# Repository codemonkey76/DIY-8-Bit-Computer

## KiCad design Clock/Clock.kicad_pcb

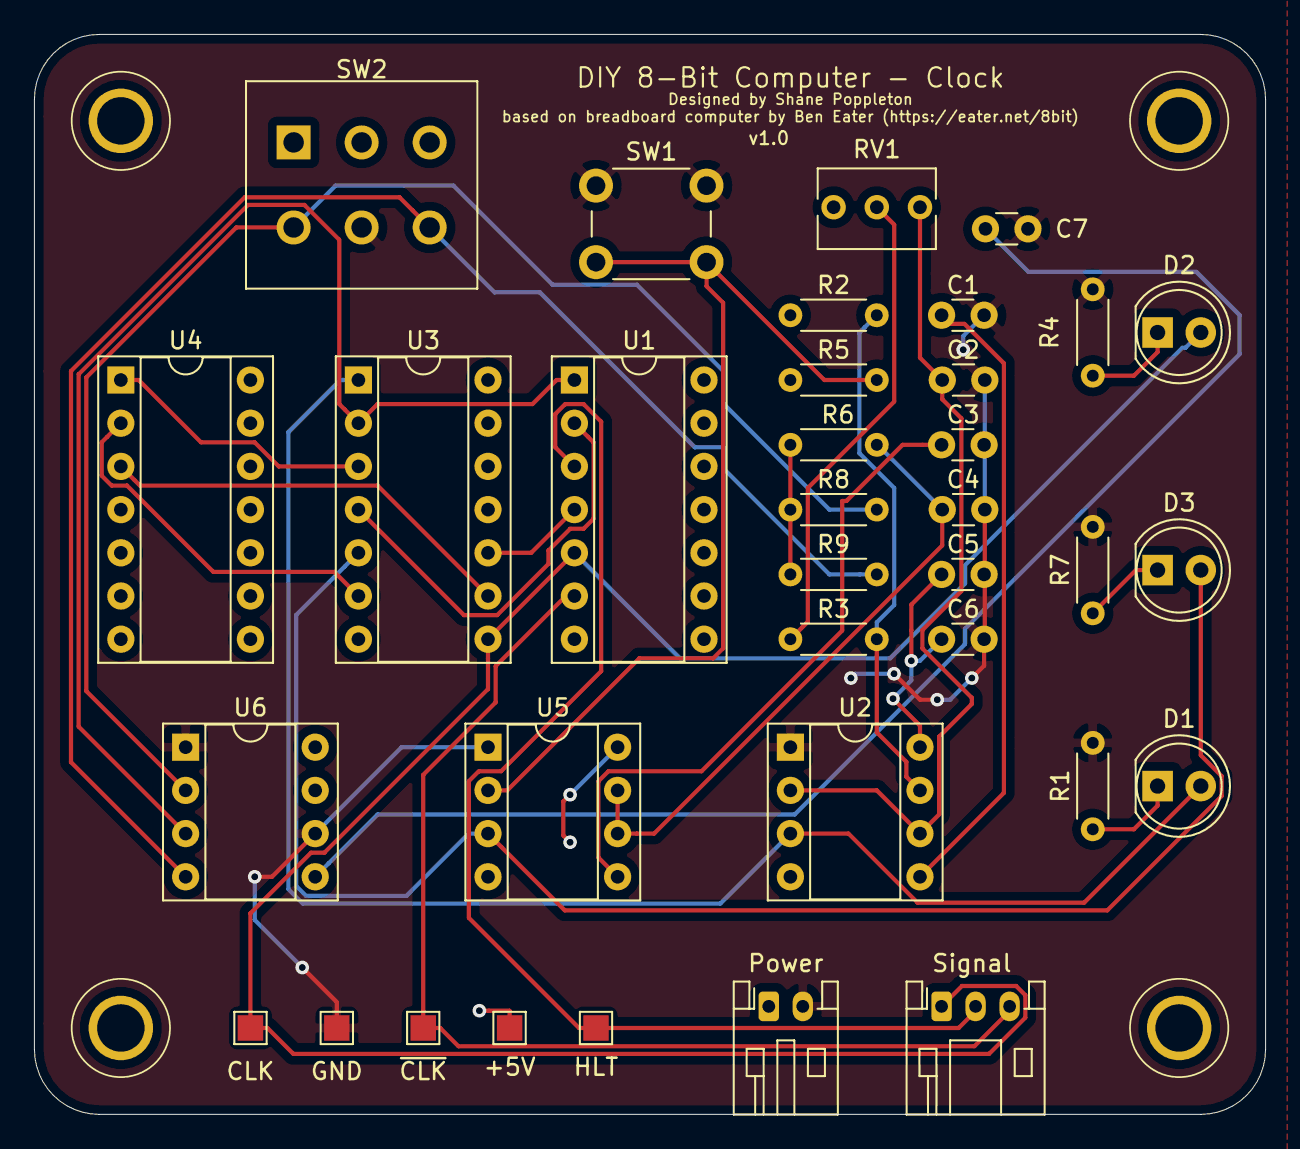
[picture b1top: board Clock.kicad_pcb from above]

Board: 2 copper layers, 72.4 x 63.5 mm, 35 parts (0 on the bottom side), 26 nets.

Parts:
C1, C3, C4, C7: 10nF; C_Disc_D3.0mm_W1.6mm_P2.50mm
C2, C5, C6: 100nF; C_Disc_D3.0mm_W1.6mm_P2.50mm
D1, D2, D3: YELLOW; LED_D5.0mm
J1: Power; JST_PH_S2B-PH-K_1x02_P2.00mm_Horizontal
J2: Signal; JST_PH_S3B-PH-K_1x03_P2.00mm_Horizontal
R1, R4, R7: 220R; R_Axial_DIN0204_L3.6mm_D1.6mm_P5.08mm_Horizontal
R2, R3, R5, R8, R9: 1K; R_Axial_DIN0204_L3.6mm_D1.6mm_P5.08mm_Horizontal
R6: 1M; R_Axial_DIN0204_L3.6mm_D1.6mm_P5.08mm_Horizontal
RV1: 1M; Potentiometer_Bourns_3266Y_Vertical
SW1: SW_Push; SW_PUSH_6mm_H5mm
SW2: SW_DPDT_x2; SW_PUSH_E-Switch_FS5700DP_DPDT
TP1: CLK; TestPoint_Pad_1.5x1.5mm
TP2: GND; TestPoint_Pad_1.5x1.5mm
TP3: ~CLK~; TestPoint_Pad_1.5x1.5mm
TP4: +5V; TestPoint_Pad_1.5x1.5mm
TP5: HLT; TestPoint_Pad_1.5x1.5mm
U1: 74LS04; DIP-14_W7.62mm_Socket
U2, U5, U6: LM555; DIP-8_W7.62mm_Socket
U3: 74LS08; DIP-14_W7.62mm_Socket
U4: 74LS32; DIP-14_W7.62mm_Socket

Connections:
+5V: C5.1, C6.1, J1.1, R2.1, R5.2, R6.1, R8.1, R9.2, TP4.1, U2.4, U2.8, U5.4, U5.8, U6.8
/CLK: D2.2, J2.1, TP1.1, U1.5, U3.8
/HLT: J2.2, TP5.1, U1.3
/~CLK~: J2.3, TP3.1, U1.6
GND: C1.2, C2.2, C3.2, C4.2, C5.2, C6.2, C7.2, J1.2, R1.2, R4.1, R7.2, SW1.1, SW2.5, TP2.1, U2.1, U5.1, U6.1, U6.6
unnamed: C1.1, U2.5
unnamed: C2.1, RV1.1, U2.2, U2.6
unnamed: C3.1, U5.5
unnamed: C4.1, R6.2, U5.6, U5.7
unnamed: C7.1, U6.5
unnamed: D1.1, R1.1
unnamed: D1.2, U2.3, U3.1
unnamed: D2.1, R4.2
unnamed: D3.1, R7.1
unnamed: D3.2, U3.5, U5.3
unnamed: R2.2, R3.2, U2.7
unnamed: R3.1, RV1.2
unnamed: R5.1, SW1.2, U5.2
unnamed: R8.2, SW2.4, U6.2
unnamed: R9.1, SW2.6, U6.4
unnamed: U1.1, U3.2, U6.3
unnamed: U1.2, U3.4
unnamed: U1.4, U3.10
unnamed: U3.3, U4.1
unnamed: U3.6, U4.2
unnamed: U3.9, U4.3

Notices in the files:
Clock/Clock.kicad_pcb:
License CC by 4.0
